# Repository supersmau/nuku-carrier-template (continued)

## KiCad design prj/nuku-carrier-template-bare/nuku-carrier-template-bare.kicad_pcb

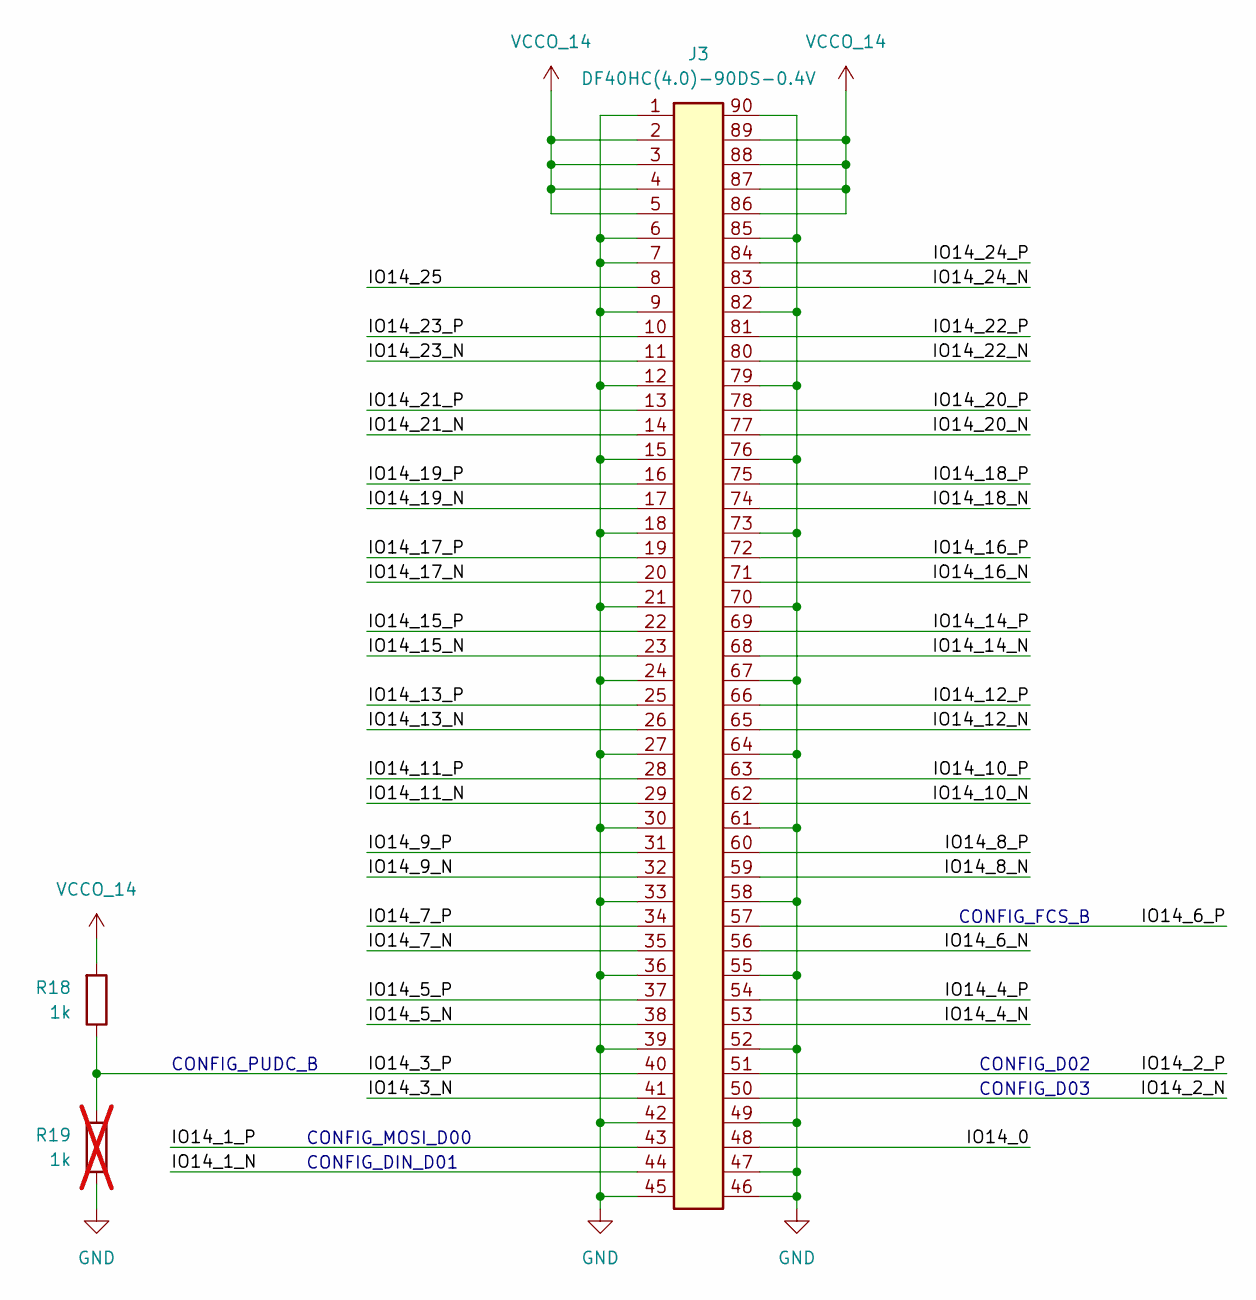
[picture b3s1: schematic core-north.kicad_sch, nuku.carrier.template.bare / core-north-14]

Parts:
J3: DF40HC(4.0)-90DS-0.4V; LCSC C597947
R18: 1k; R_0402_1005Metric; LCSC C11702
R19: 1k; R_0402_1005Metric; LCSC C11702; not fitted

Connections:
/core-north-14/IO14_0: J3.48
/core-north-14/IO14_1_N: J3.44
/core-north-14/IO14_1_P: J3.43
/core-north-14/IO14_2_N: J3.50
/core-north-14/IO14_2_P: J3.51
/core-north-14/IO14_3_N: J3.41
/core-north-14/IO14_3_P: J3.40, R18.1, R19.2
/core-north-14/IO14_4_N: J3.53
/core-north-14/IO14_4_P: J3.54
/core-north-14/IO14_5_N: J3.38
/core-north-14/IO14_5_P: J3.37
/core-north-14/IO14_6_N: J3.56
/core-north-14/IO14_6_P: J3.57
/core-north-14/IO14_7_N: J3.35
/core-north-14/IO14_7_P: J3.34
/core-north-14/IO14_8_N: J3.59
/core-north-14/IO14_8_P: J3.60
/core-north-14/IO14_9_N: J3.32
/core-north-14/IO14_9_P: J3.31
/core-north-14/IO14_10_N: J3.62
/core-north-14/IO14_10_P: J3.63
/core-north-14/IO14_11_N: J3.29
/core-north-14/IO14_11_P: J3.28
/core-north-14/IO14_12_N: J3.65
/core-north-14/IO14_12_P: J3.66
/core-north-14/IO14_13_N: J3.26
/core-north-14/IO14_13_P: J3.25
/core-north-14/IO14_14_N: J3.68
/core-north-14/IO14_14_P: J3.69
/core-north-14/IO14_15_N: J3.23
/core-north-14/IO14_15_P: J3.22
/core-north-14/IO14_16_N: J3.71
/core-north-14/IO14_16_P: J3.72
/core-north-14/IO14_17_N: J3.20
/core-north-14/IO14_17_P: J3.19
/core-north-14/IO14_18_N: J3.74
/core-north-14/IO14_18_P: J3.75
/core-north-14/IO14_19_N: J3.17
/core-north-14/IO14_19_P: J3.16
/core-north-14/IO14_20_N: J3.77
/core-north-14/IO14_20_P: J3.78
/core-north-14/IO14_21_N: J3.14
/core-north-14/IO14_21_P: J3.13
/core-north-14/IO14_22_N: J3.80
/core-north-14/IO14_22_P: J3.81
/core-north-14/IO14_23_N: J3.11
/core-north-14/IO14_23_P: J3.10
/core-north-14/IO14_24_N: J3.83
/core-north-14/IO14_24_P: J3.84
/core-north-14/IO14_25: J3.8
GND: J3.1, J3.6, J3.7, J3.9, J3.12, J3.15, J3.18, J3.21, J3.24, J3.27, J3.30, J3.33, J3.36, J3.39, J3.42, J3.45, J3.46, J3.47, J3.49, J3.52, J3.55, J3.58, J3.61, J3.64, J3.67, J3.70, J3.73, J3.76, J3.79, J3.82, J3.85, J3.90, R19.1; also elsewhere on the board
VCCO_14: J3.2, J3.3, J3.4, J3.5, J3.86, J3.87, J3.88, J3.89, R18.2

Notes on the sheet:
CONFIG_DIN_D01
CONFIG_D02
CONFIG_D03
CONFIG_FCS_B
CONFIG_PUDC_B
CONFIG_MOSI_D00

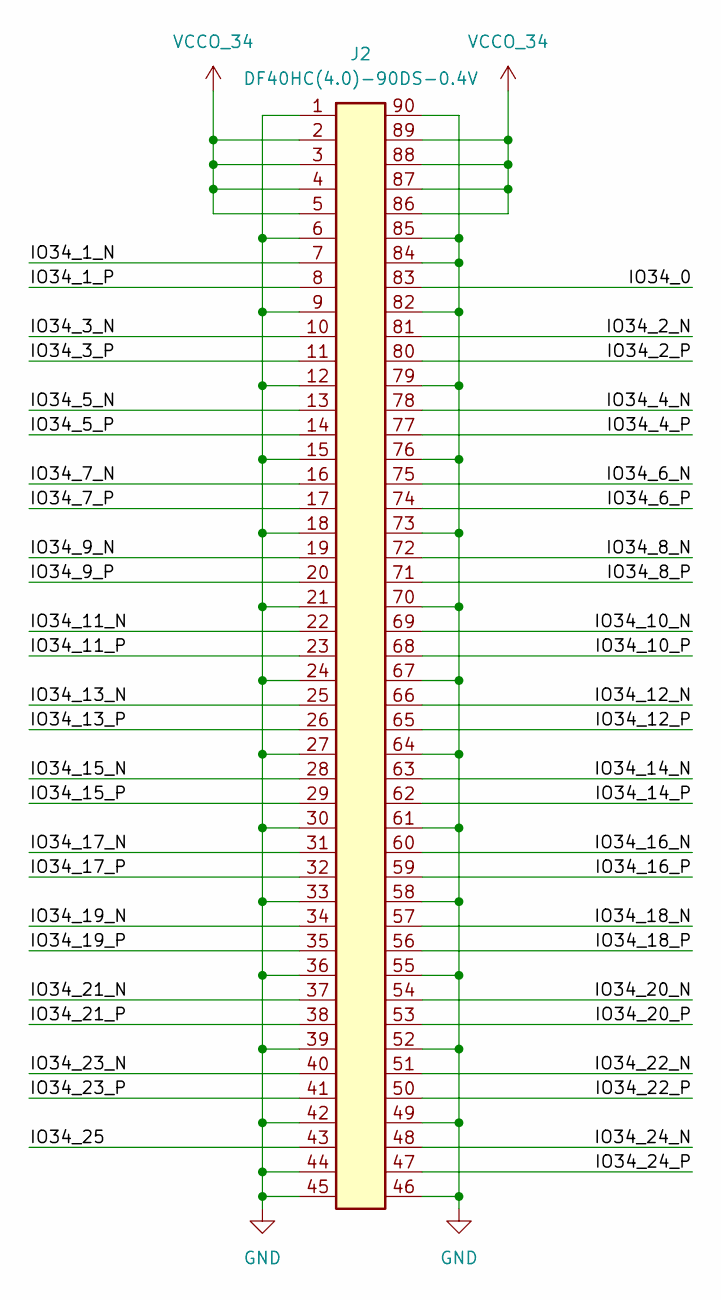
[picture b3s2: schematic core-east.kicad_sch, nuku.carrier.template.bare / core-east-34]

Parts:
J2: DF40HC(4.0)-90DS-0.4V; LCSC C597947

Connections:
/core-east-34/IO34_0: J2.83
/core-east-34/IO34_1_N: J2.7
/core-east-34/IO34_1_P: J2.8
/core-east-34/IO34_2_N: J2.81
/core-east-34/IO34_2_P: J2.80
/core-east-34/IO34_3_N: J2.10
/core-east-34/IO34_3_P: J2.11
/core-east-34/IO34_4_N: J2.78
/core-east-34/IO34_4_P: J2.77
/core-east-34/IO34_5_N: J2.13
/core-east-34/IO34_5_P: J2.14
/core-east-34/IO34_6_N: J2.75
/core-east-34/IO34_6_P: J2.74
/core-east-34/IO34_7_N: J2.16
/core-east-34/IO34_7_P: J2.17
/core-east-34/IO34_8_N: J2.72
/core-east-34/IO34_8_P: J2.71
/core-east-34/IO34_9_N: J2.19
/core-east-34/IO34_9_P: J2.20
/core-east-34/IO34_10_N: J2.69
/core-east-34/IO34_10_P: J2.68
/core-east-34/IO34_11_N: J2.22
/core-east-34/IO34_11_P: J2.23
/core-east-34/IO34_12_N: J2.66
/core-east-34/IO34_12_P: J2.65
/core-east-34/IO34_13_N: J2.25
/core-east-34/IO34_13_P: J2.26
/core-east-34/IO34_14_N: J2.63
/core-east-34/IO34_14_P: J2.62
/core-east-34/IO34_15_N: J2.28
/core-east-34/IO34_15_P: J2.29
/core-east-34/IO34_16_N: J2.60
/core-east-34/IO34_16_P: J2.59
/core-east-34/IO34_17_N: J2.31
/core-east-34/IO34_17_P: J2.32
/core-east-34/IO34_18_N: J2.57
/core-east-34/IO34_18_P: J2.56
/core-east-34/IO34_19_N: J2.34
/core-east-34/IO34_19_P: J2.35
/core-east-34/IO34_20_N: J2.54
/core-east-34/IO34_20_P: J2.53
/core-east-34/IO34_21_N: J2.37
/core-east-34/IO34_21_P: J2.38
/core-east-34/IO34_22_N: J2.51
/core-east-34/IO34_22_P: J2.50
/core-east-34/IO34_23_N: J2.40
/core-east-34/IO34_23_P: J2.41
/core-east-34/IO34_24_N: J2.48
/core-east-34/IO34_24_P: J2.47
/core-east-34/IO34_25: J2.43
GND: J2.1, J2.6, J2.9, J2.12, J2.15, J2.18, J2.21, J2.24, J2.27, J2.30, J2.33, J2.36, J2.39, J2.42, J2.44, J2.45, J2.46, J2.49, J2.52, J2.55, J2.58, J2.61, J2.64, J2.67, J2.70, J2.73, J2.76, J2.79, J2.82, J2.84, J2.85, J2.90; also elsewhere on the board
VCCO_34: J2.2, J2.3, J2.4, J2.5, J2.86, J2.87, J2.88, J2.89

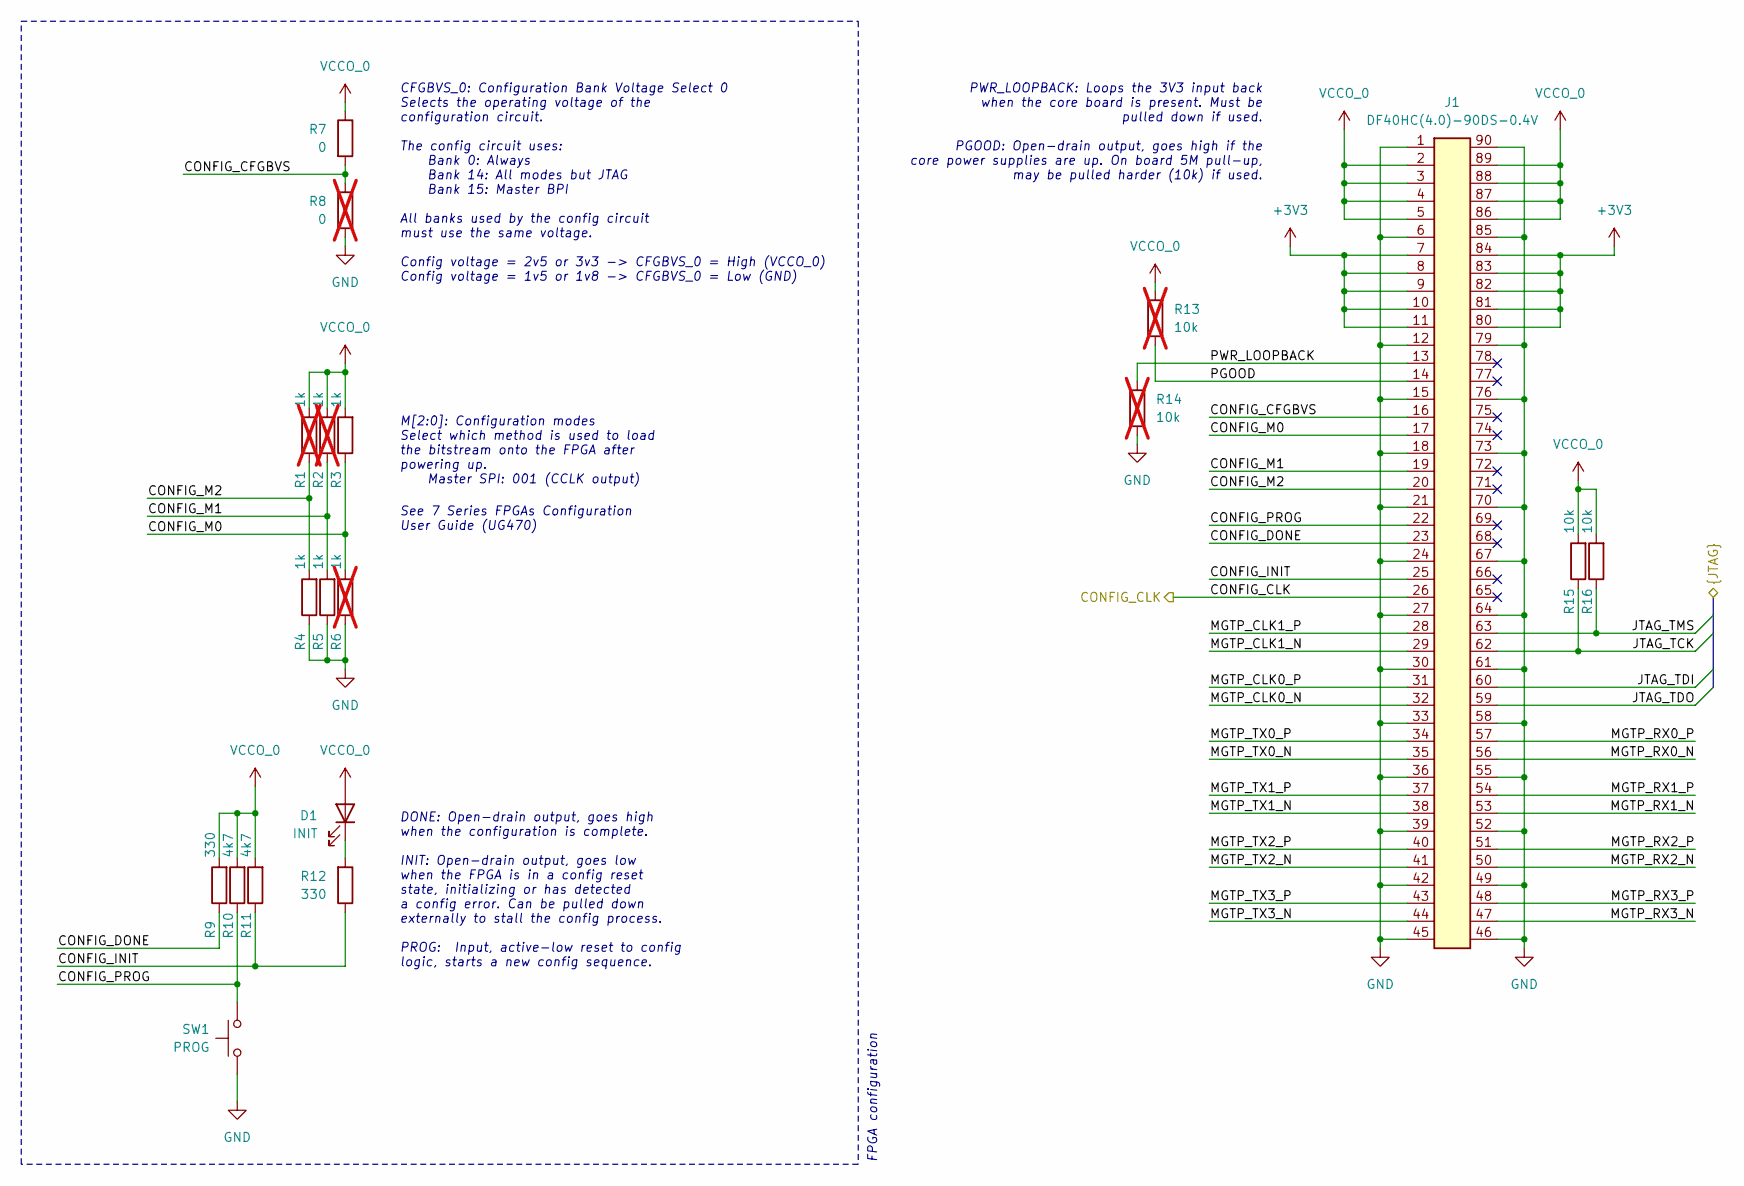
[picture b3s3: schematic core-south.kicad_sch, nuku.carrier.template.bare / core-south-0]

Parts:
D1: INIT; LED_0805_2012Metric; LCSC C2297
J1: DF40HC(4.0)-90DS-0.4V; LCSC C597947
R1, R2, R6: 1k; R_0402_1005Metric; LCSC C11702; not fitted
R3, R4, R5: 1k; R_0402_1005Metric; LCSC C11702
R7: 0; R_0402_1005Metric; LCSC C17168
R8: 0; R_0402_1005Metric; LCSC C17168; not fitted
R9, R12: 330; R_0402_1005Metric; LCSC C25104
R10, R11: 4k7; R_0402_1005Metric; LCSC C25900
R13, R14: 10k; R_0402_1005Metric; LCSC C25744; not fitted
R15, R16: 10k; R_0402_1005Metric; LCSC C25744
SW1: PROG; TS-1088-AR02016; LCSC C720477

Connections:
+3V3: J1.7, J1.8, J1.9, J1.10, J1.11, J1.80, J1.81, J1.82, J1.83, J1.84
/core-south-0/CONFIG_CFGBVS: J1.16, R7.2, R8.1
/core-south-0/CONFIG_CLK: J1.26
/core-south-0/CONFIG_DONE: J1.23, R9.1
/core-south-0/CONFIG_INIT: J1.25, R11.1, R12.1
/core-south-0/CONFIG_M0: J1.17, R3.1, R6.2
/core-south-0/CONFIG_M1: J1.19, R2.1, R5.2
/core-south-0/CONFIG_M2: J1.20, R1.1, R4.2
/core-south-0/CONFIG_PROG: J1.22, R10.1, SW1.2
/core-south-0/JTAG_TCK: J1.62, R15.1
/core-south-0/JTAG_TDI: J1.60
/core-south-0/JTAG_TDO: J1.59
/core-south-0/JTAG_TMS: J1.63, R16.1
/core-south-0/MGTP_CLK1_N: J1.29
/core-south-0/MGTP_CLK1_P: J1.28
/core-south-0/MGTP_RX0_N: J1.56
/core-south-0/MGTP_RX0_P: J1.57
/core-south-0/MGTP_RX1_N: J1.53
/core-south-0/MGTP_RX1_P: J1.54
/core-south-0/MGTP_RX2_N: J1.50
/core-south-0/MGTP_RX2_P: J1.51
/core-south-0/MGTP_RX3_N: J1.47
/core-south-0/MGTP_RX3_P: J1.48
/core-south-0/MGTP_TX0_N: J1.35
/core-south-0/MGTP_TX0_P: J1.34
/core-south-0/MGTP_TX1_N: J1.38
/core-south-0/MGTP_TX1_P: J1.37
/core-south-0/MGTP_TX2_N: J1.41
/core-south-0/MGTP_TX2_P: J1.40
/core-south-0/MGTP_TX3_N: J1.44
/core-south-0/MGTP_TX3_P: J1.43
/core-south-0/PGOOD: J1.14, R13.1
/core-south-0/PWR_LOOPBACK: J1.13, R14.2
GND: J1.1, J1.6, J1.12, J1.15, J1.18, J1.21, J1.24, J1.27, J1.30, J1.33, J1.36, J1.39, J1.42, J1.45, J1.46, J1.49, J1.52, J1.55, J1.58, J1.61, J1.64, J1.67, J1.70, J1.73, J1.76, J1.79, J1.85, J1.90, R4.1, R5.1, R6.1, R8.2, R14.1, SW1.1; also elsewhere on the board
unnamed: D1.1 (K), R12.2
VCCO_0: D1.2 (A), J1.2, J1.3, J1.4, J1.5, J1.86, J1.87, J1.88, J1.89, R1.2, R2.2, R3.2, R7.1, R9.2, R10.2, R11.2, R13.2, R15.2, R16.2

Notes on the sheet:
M[2:0]: Configuration modes Select which method is used to load the bitstream onto the FPGA after powering up. Master SPI: 001 (CCLK output)
FPGA configuration
See 7 Series FPGAs Configuration User Guide (UG470)
DONE: Open-drain output, goes high when the configuration is complete. INIT: Open-drain output, goes low when the FPGA is in a config reset state, initializing or has detected a config error. Can be pulled down externally to stall the config process. PROG: Input, active-low reset to config logic, s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
CFGBVS_0: Configuration Bank Voltage Select 0 Selects the operating voltage of the configuration circuit. The config circuit uses: Bank 0: Always Bank 14: All modes but JTAG Bank 15: Master BPI All banks used by the config circuit must use the same voltage. Config voltage = 2v5 or 3v3 -> CFGBVS_0 =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
PWR_LOOPBACK: Loops the 3V3 input back when the core board is present. Must be pulled down if used. PGOOD: Open-drain output, goes high if the core power supplies are up. On board 5M pull-up, may be pulled harder (10k) if used.

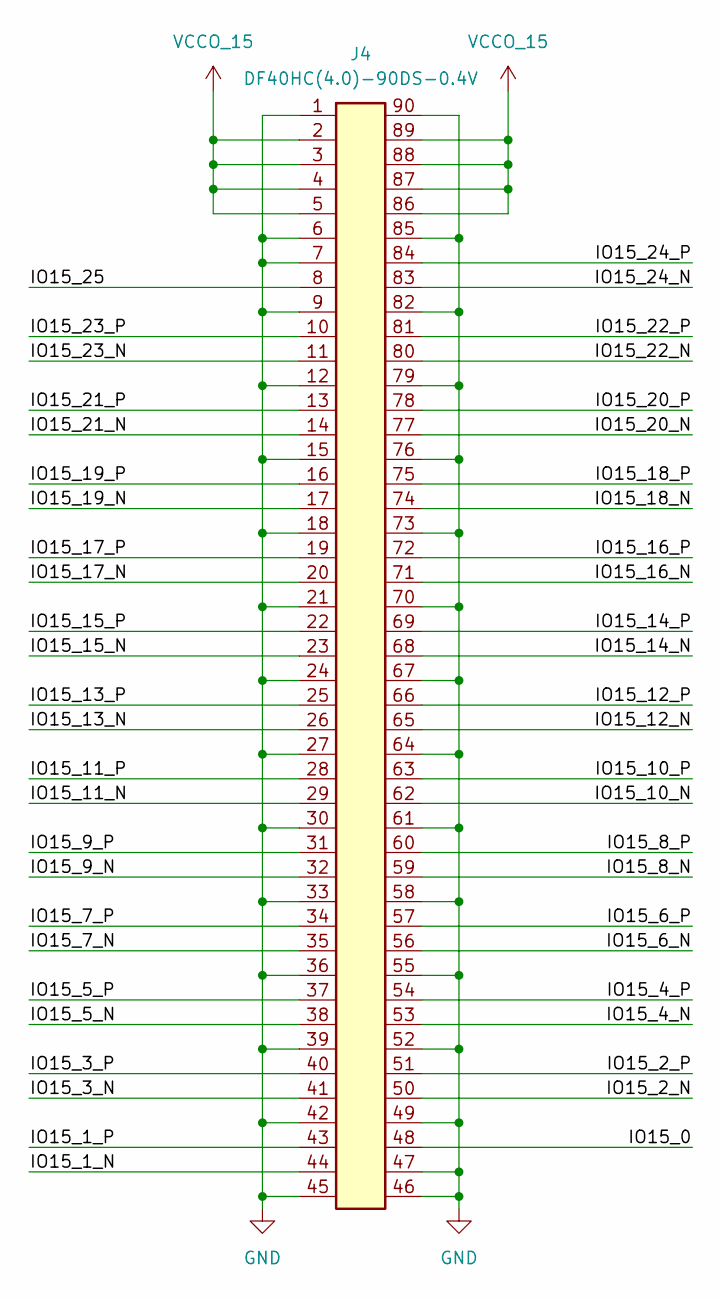
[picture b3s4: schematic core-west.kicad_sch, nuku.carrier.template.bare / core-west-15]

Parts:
J4: DF40HC(4.0)-90DS-0.4V; LCSC C597947

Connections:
/core-west-15/IO15_0: J4.48
/core-west-15/IO15_1_N: J4.44
/core-west-15/IO15_1_P: J4.43
/core-west-15/IO15_2_N: J4.50
/core-west-15/IO15_2_P: J4.51
/core-west-15/IO15_3_N: J4.41
/core-west-15/IO15_3_P: J4.40
/core-west-15/IO15_4_N: J4.53
/core-west-15/IO15_4_P: J4.54
/core-west-15/IO15_5_N: J4.38
/core-west-15/IO15_5_P: J4.37
/core-west-15/IO15_6_N: J4.56
/core-west-15/IO15_6_P: J4.57
/core-west-15/IO15_7_N: J4.35
/core-west-15/IO15_7_P: J4.34
/core-west-15/IO15_8_N: J4.59
/core-west-15/IO15_8_P: J4.60
/core-west-15/IO15_9_N: J4.32
/core-west-15/IO15_9_P: J4.31
/core-west-15/IO15_10_N: J4.62
/core-west-15/IO15_10_P: J4.63
/core-west-15/IO15_11_N: J4.29
/core-west-15/IO15_11_P: J4.28
/core-west-15/IO15_12_N: J4.65
/core-west-15/IO15_12_P: J4.66
/core-west-15/IO15_13_N: J4.26
/core-west-15/IO15_13_P: J4.25
/core-west-15/IO15_14_N: J4.68
/core-west-15/IO15_14_P: J4.69
/core-west-15/IO15_15_N: J4.23
/core-west-15/IO15_15_P: J4.22
/core-west-15/IO15_16_N: J4.71
/core-west-15/IO15_16_P: J4.72
/core-west-15/IO15_17_N: J4.20
/core-west-15/IO15_17_P: J4.19
/core-west-15/IO15_18_N: J4.74
/core-west-15/IO15_18_P: J4.75
/core-west-15/IO15_19_N: J4.17
/core-west-15/IO15_19_P: J4.16
/core-west-15/IO15_20_N: J4.77
/core-west-15/IO15_20_P: J4.78
/core-west-15/IO15_21_N: J4.14
/core-west-15/IO15_21_P: J4.13
/core-west-15/IO15_22_N: J4.80
/core-west-15/IO15_22_P: J4.81
/core-west-15/IO15_23_N: J4.11
/core-west-15/IO15_23_P: J4.10
/core-west-15/IO15_24_N: J4.83
/core-west-15/IO15_24_P: J4.84
/core-west-15/IO15_25: J4.8
GND: J4.1, J4.6, J4.7, J4.9, J4.12, J4.15, J4.18, J4.21, J4.24, J4.27, J4.30, J4.33, J4.36, J4.39, J4.42, J4.45, J4.46, J4.47, J4.49, J4.52, J4.55, J4.58, J4.61, J4.64, J4.67, J4.70, J4.73, J4.76, J4.79, J4.82, J4.85, J4.90; also elsewhere on the board
VCCO_15: J4.2, J4.3, J4.4, J4.5, J4.86, J4.87, J4.88, J4.89

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
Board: 4 copper layers, 24 parts (0 on the bottom side), 20 nets, no tracks yet.

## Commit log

2025-06-08 Nuku carrier template
2025-06-22 Add basic template
2025-06-22 Route template.basic
2025-06-23 Placement basic
2025-06-25 Finish template.basic + Production outputs
2025-06-29 Finish bridgeless template
2025-06-29 Minor tweaks
2025-06-30 Tweaks
2025-07-01 Finish boards - prod ready
